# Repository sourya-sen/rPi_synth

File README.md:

**A 32HP EURORACK VIDEO SYNTHESISER**

Update (August 2019): This was the subject of my Master's thesis at Aalto Media Lab and the written thesis can be found and downloaded from [here](https://aaltodoc.aalto.fi/handle/123456789/38068).

The project is currently on hold as I want to upgrade and test with a Raspberry Pi 4 for performance benefits as well as update the hardware with a few fixes and design strategies that were found to be lacking in the current version. However, this version continues to work and if you are looking to build and run one for yourself, I am available to help in any troubleshooting.

[Here is the unit in action as part of my an audiovisual performance at Live Performers Meet 2018.](https://vimeo.com/277031718/060efab75c)

**NOTE: THIS IS STILL WORK IN PROGRESS, PROCEED AT YOUR OWN RISK! TO SUCCESSFULLY RUN, YOU WILL NEED A FABRICATED PCB, A RASPBERRY PI (TESTED WITH RPI 3) AND A EURORACK SETUP.**

## Introduction
This is the central repository for the Hybrid Video Synthesiser project.

The Hybrid Video Synthesiser, as the name suggests, is a video synthesiser that has digital brains by using a Raspberry Pi but can interface with any analog signal for sequencing, manipulating and/or modulating. This version is compatible with Eurorack standards.

It is made up of the following ingredients.
1. A custom PCB to interface between the Eurorack signals and the Raspberry Pi, both EAGLE files and gerbers are made available in the `Hardware` folder.

2. The `rPi_Framework` openFrameworks application that communicates between the hardware and the Raspberry Pi and sends the current state over OSC to the system.

3. The `rPi_videoSynth` openFrameworks application that listens to the OSC communication and runs the visuals. The visuals themselves are fragment shaders that reside in the `/rPi_videoSynth/bin/data/shaders` folder.

4. A illustrator file for the front panel, in the `Hardware` folder.

And the following extras,
* Scripts to auto run on boot on a Raspberry Pi.

* A desktop GUI simulating the hardware OSC communication for testing without the hardware. The `synth_CVTester` openFrameworks application handles that. **IMPORTANT: If using the videoSynth application on the desktop, use the relevant shader headers. See the install notes below - the only difference is using the desktop shader headers instead of the pi headers in step 4.**

The hardware has 4 CV inputs and 8 Gate inputs.

Design wise, the synthesiser is designed to run 8 visual 'systems', as selected by the system toggles in binary fashion. (Refer to conversion chart on front panel).

Each system has 4 sub systems, set by the 2 sub system toggles, again in binary fashion.

The last three toggles/gates switch on/off an effects patch (not implemented yet), a white strobe and enable/disable the final image (useful for black strobes!).

Each can be selected by the toggle switches, but plugging in a gate signal overrides the toggle switch.

Each visual system (and it's subsequent sub system) have 4 parameters that can be controlled by the potentiometers. They also allow CV input and when CV input is present, the potentiometers become attenuators for the CV input. The range and response of the CV inputs (unipolar, bipolar, exponential) can be changed, they're currently hardcoded in the software but will be replaced by an user editable XML file in a later revision.

## About the Hardware
The schematics are available in the `Documentation` folder.

The functionality of the PCB is described below.

The MCP3008 A-to-D chip is used to handle analog inputs coming into the Pi. The CV inputs are taken through an op-amp differential circuit to scale -5V to +5V signals to 0-3.3V Raspberry Pi friendly levels before going into the chip. Any signals below or above the mentioned range is discarded.

The final CV parameter in the software is the value of `potentiometer * CV input` for each channel. When an input CV is missing, the jacks are normalised to +5V to get a constant value of 1.

**Note: Known issue here. As the reference 5V is taken from the Pi's 5V, when plugging in a CV signal, the switching jack doesn't switch cleanly and a different voltage touching the 5V rail of the Pi makes the Pi restart. This will be fixed in the following revision - currently it requires cutting a trace and attaching a 5V regulator from the 12V power rail instead of using the 5V rPi rail.**

The 0-3.3V incoming value is translated to a value of 0-1023 on the software side, which is further mapped to 0.0-1.0 if using the bipolar mode. It is possible to change how the CV is handled, ie, setting it to unipolar by changing a few lines of code, as below:

```
CVin[4].setExponential();
CVin[6].setUnipolar();
CVin[7].setUnipolar();
```

where CVin[0] - CVin[3] are the potentiometer values and CVin[4] - CVin[7] are the CV inputs. The default setting is bipolar. This is currently set in `ofApp::setup()` of `rPi_videoSynth` but will be available to be setup from an XML file in a later revision.

There are two comparators checking the current toggle states of the gates/switches. These go through a multiplexer into the rPi. The comparators are checking for any values above 2.5V but this can be changed by changing R11 and R12.

**Note: Know limitation, the toggles don't activate with very short triggers from the Eurorack, even if the LEDs light up. This _may_ or _may not_ be fixable. To be investigated further. But this arises from the timing differences of the frames per second refresh cycle of the visuals v/s the asynchronous hardware communication.**

## Installing
**Note: I will make a disk image available eventually that can be burned directly to a microSD card, but currently the only way to run this is to install from github.**

This guide assumes you are running the latest version of Raspbian Stretch and have openFrameworks 0.10.0 installed and compiled. This guide also assumes that openFrameworks is installed at `/home/pi/openFrameworks` and the boot options are set to `Console Autologin`.

1. Get the [ofxGPIO](https://github.com/kashimAstro/ofxGPIO) addon.
  * Navigate to `openFrameworks/addons`
  * Clone the ofxGPIO library by typing `git clone https://github.com/kashimAstro/ofxGPIO` and press Enter.

2. Clone this repository.
  * Navigate to `openFrameworks/apps` (Note: Just apps, not myApps).
  * Type `git clone https://github.com/sourya-sen/rPi_synth` and press Enter.

3. Compile **both** the apps separately.
  * Navigate to `openFrameworks/apps/rPi_synth/rPi_Framework`
  * Type `sudo make`, wait for it to finish compiling.
  * Navigate to `openFrameworks/apps/rPi_synth/rPi_videoSynth`
  * Type `sudo make`, wait for it to finish compiling.

4. Copy the header files required to run the shaders.
  * type `cp /home/pi/openFrameworks/apps/rPi_synth/Resources/shaderHeaders/pi/* /home/pi/openFrameworks/apps/rPi_synth/rPi_videoSynth/bin/data/shaders` and hit Enter.

If everything went well, at this point you should be ready to run the video synth!

## Running
The easiest way to run the two softwares that run the video synth is to use the `runSynth` script.

  * Type `cp /home/pi/openFrameworks/apps/rPi_synth/Resources/runSynth.sh /home/pi` and hit Enter.
  * Make sure you're on the bottom level of the pi user account by typing `cd` and hitting Enter.
  * Make the script executable by typing `chmod +x runSynth.sh`
  * Run the synth by typing `./runSynth` and hitting Enter!

To avoid having to run the video synth by running the command with a keyboard every time, you can make the Pi run the `runSynth` script on startup by adding it to the `rc.local` file.

  * Type `sudo nano /etc/rc.local` and hit Enter.
  * Add `sh /home/pi/runSynth.sh &` at the end of the file.
  * Save the file and exit.

Now, every time the Raspberry Pi is switched on, it will boot directly into the synth!

## Writing Own Visuals
If you know how to write fragment shaders, you already know how to write your own visuals! It is also easy to port shaders from [glslsandbox](http://glslsandbox.com/) or [shadertoy](https://www.shadertoy.com/) with some minor changes. The only difference is using the cross platform shader syntax, which you can refer to [here](https://github.com/sourya-sen/oF_crossPlatformShaderExample) for an example. As long as the shaders are named correctly (refer to the existing shader files), they will be available as 'systems' corresponding to the file number. The `.vert` file is common to each fragment shader.

The shaders have multiple uniforms available to them for use. Refer to any preexisting shaders for reference. The shaders are loaded at run time when the application is run and switch accordingly depending on the selected 'system' either through the panel controls or through gate inputs. It is also possible to reload the shaders in the application by pressing `R` on the keyboard. This is handy if you are testing the shaders in the Desktop environment.

In case you need a tutorial on how to write fragment shaders, I'd recommend going through [The Book of Shaders](https://thebookofshaders.com/).

**NOTE: Due to the limited graphics performance capabilities of the Raspberry Pi, it is recommended to thoroughly test each new shader. If a keyboard is attached to the Pi in the testing process, pressing `spacebar` would draw debug strings which will show you the current fps and other relevant data.**

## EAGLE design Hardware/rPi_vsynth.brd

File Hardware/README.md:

The .sch and .brd files here are designs for the PCB, last updated with Eagle 8.5.0.

Please check the main README for known issues with the current hardware revision version.

Library parts used here are from the [Music Thing Modular parts library by Tom Whitwell](https://github.com/TomWhitwell/MTM-Parts-Library) and the [Sparkfun Library](https://github.com/sparkfun/SparkFun-Eagle-Libraries).

The gerber (currently v0.2) files in the zipped folder have been used to fabricate PCBs from [Seeed Fusion PCB Services](https://www.seeedstudio.com/fusion.html) and generated with the Seeed Gerber Generator and the board adheres to the Seeed Design Rules, both found [here](http://support.seeedstudio.com/knowledgebase/articles/422482-fusion-pcb-pcba-order-submission-guidelines).

**[TODO: Add image of the PCB?]**

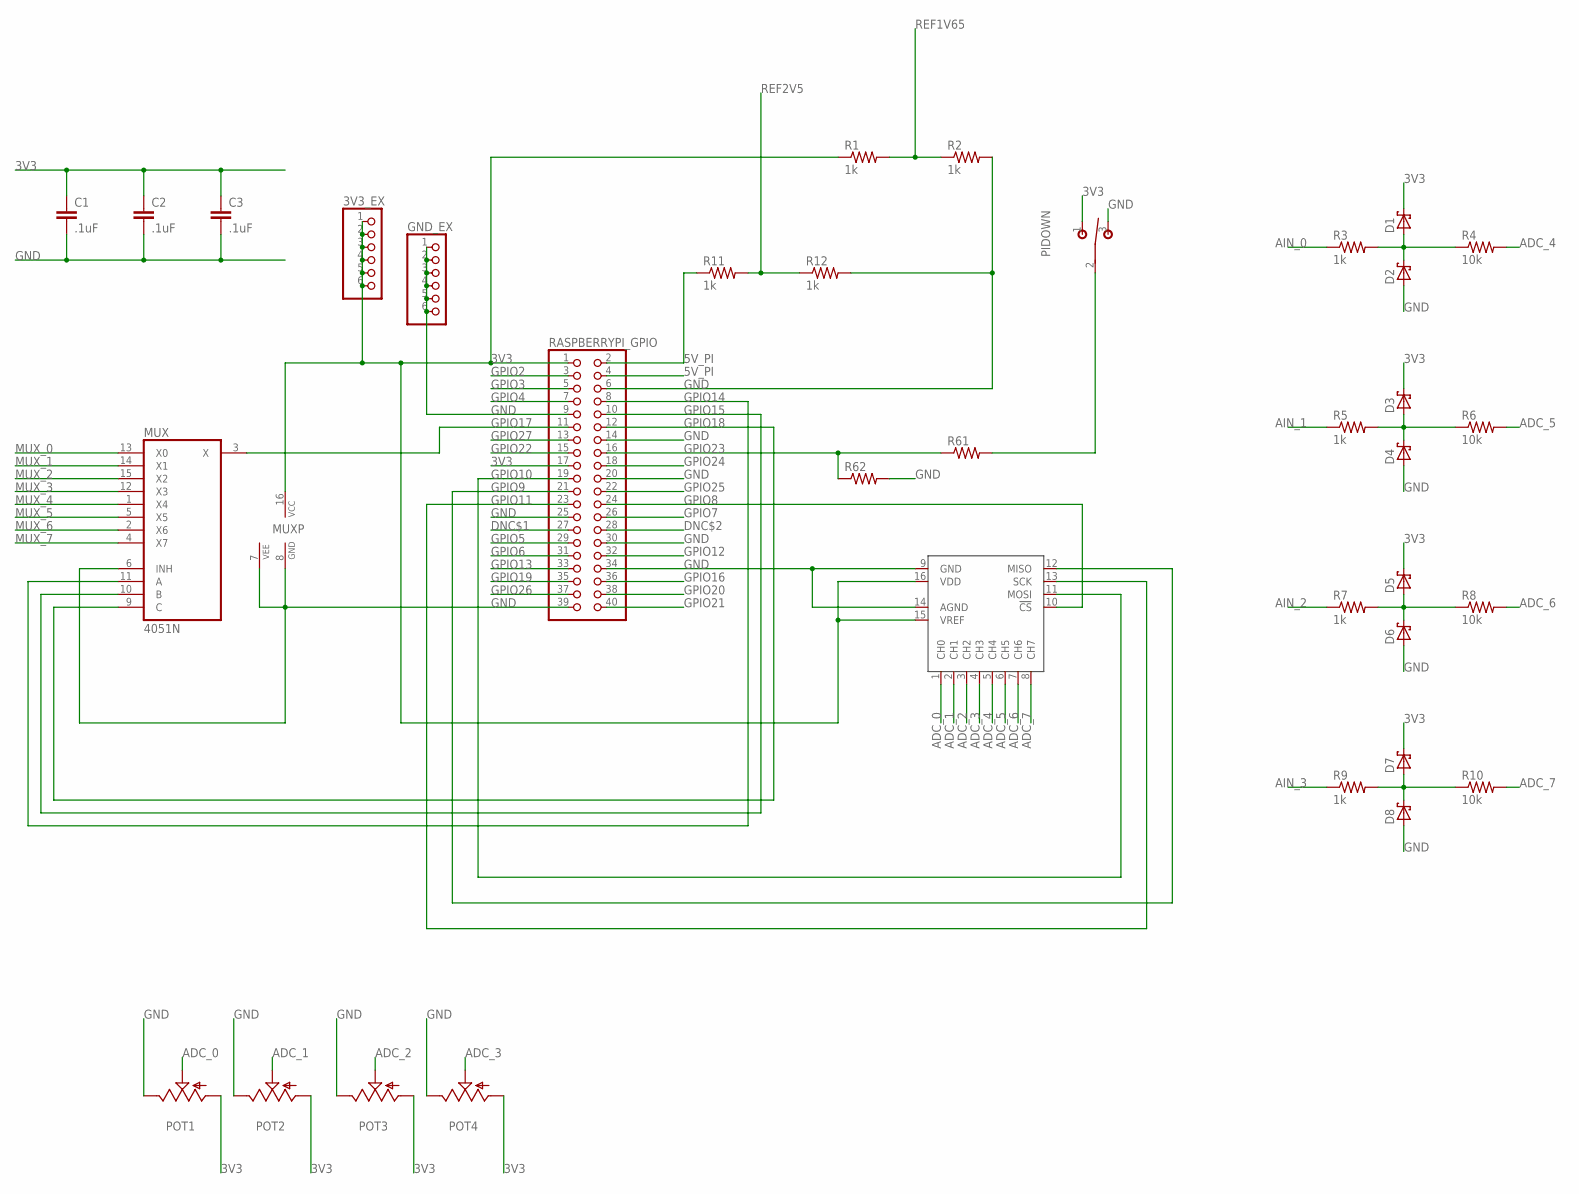
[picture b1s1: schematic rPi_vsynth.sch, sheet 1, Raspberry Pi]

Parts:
3V3_EX: PINHD-1X6B; 1X06-BIG
C1, C2, C3: .1uF; CAP-PTH-SMALL2
D1, D2, D3, D4, D5, D6, D7, D8: SCHOTTKY-DIODEDO35-7; DO35-7
GND_EX: PINHD-1X6B; 1X06-BIG
MCP3008: MCP3008P; DIL16
MUX: 4051N; DIL16
PIDOWN: T-80-T-SPDT-ON-OFF-ON; M9040P
POT1, POT2, POT3, POT4: 9MM_SNAP-IN_POT_; 9MM_SNAP-IN_POT
R1, R2, R3, R5, R7, R9, R11, R12: 1k; AXIAL-0.4
R4, R6, R8, R10: 10k; AXIAL-0.4
R61, R62: RESISTORPTH-1/4W; AXIAL-0.4
RASPBERRYPI_GPIO: PINHD-2X20; 2X20

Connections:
3V3: 3V3_EX.1, 3V3_EX.2, 3V3_EX.3, 3V3_EX.4, 3V3_EX.5, 3V3_EX.6, C1.1, C2.1, C3.1, D1.C, D3.C, D5.C, D7.C, MCP3008.15 (VREF), MCP3008.16 (VDD), MUX.16 (VCC), PIDOWN.1 (O), POT1.1 (A), POT2.1 (A), POT3.1 (A), POT4.1 (A), R1.P$1 (1), RASPBERRYPI_GPIO.1, RASPBERRYPI_GPIO.17; also elsewhere on the board
5V_PI: R11.P$1 (1), RASPBERRYPI_GPIO.2, RASPBERRYPI_GPIO.4; also elsewhere on the board
ADC_0: MCP3008.1 (CH0), POT1.2 (S)
ADC_1: MCP3008.2 (CH1), POT2.2 (S)
ADC_2: MCP3008.3 (CH2), POT3.2 (S)
ADC_3: MCP3008.4 (CH3), POT4.2 (S)
ADC_4: MCP3008.5 (CH4), R4.P$2 (2)
ADC_5: MCP3008.6 (CH5), R6.P$2 (2)
ADC_6: MCP3008.7 (CH6), R8.P$2 (2)
ADC_7: MCP3008.8 (CH7), R10.P$2 (2)
AIN_0: R3.P$1 (1); also elsewhere on the board
AIN_1: R5.P$1 (1); also elsewhere on the board
AIN_2: R7.P$1 (1); also elsewhere on the board
AIN_3: R9.P$1 (1); also elsewhere on the board
DNC$1: RASPBERRYPI_GPIO.27
DNC$2: RASPBERRYPI_GPIO.28
GND: C1.2, C2.2, C3.2, D2.A, D4.A, D6.A, D8.A, GND_EX.1, GND_EX.2, GND_EX.3, GND_EX.4, GND_EX.5, GND_EX.6, MCP3008.9 (GND), MCP3008.14 (AGND), MUX.6 (INH), MUX.7 (VEE), MUX.8 (GND), PIDOWN.3 (S), POT1.3 (E), POT2.3 (E), POT3.3 (E), POT4.3 (E), R2.P$2 (2), R12.P$2 (2), R62.P$2 (2), RASPBERRYPI_GPIO.6, RASPBERRYPI_GPIO.9, RASPBERRYPI_GPIO.14, RASPBERRYPI_GPIO.20, RASPBERRYPI_GPIO.25, RASPBERRYPI_GPIO.30, RASPBERRYPI_GPIO.34, RASPBERRYPI_GPIO.39; also elsewhere on the board
GPIO2: RASPBERRYPI_GPIO.3
GPIO3: RASPBERRYPI_GPIO.5
GPIO4: RASPBERRYPI_GPIO.7
GPIO5: RASPBERRYPI_GPIO.29
GPIO6: RASPBERRYPI_GPIO.31
GPIO7: RASPBERRYPI_GPIO.26
GPIO8: MCP3008.10 (!CS), RASPBERRYPI_GPIO.24
GPIO9: MCP3008.12 (MISO), RASPBERRYPI_GPIO.21
GPIO10: MCP3008.11 (MOSI), RASPBERRYPI_GPIO.19
GPIO11: MCP3008.13 (SCK), RASPBERRYPI_GPIO.23
GPIO12: RASPBERRYPI_GPIO.32
GPIO13: RASPBERRYPI_GPIO.33
GPIO14: MUX.11 (A), RASPBERRYPI_GPIO.8
GPIO15: MUX.10 (B), RASPBERRYPI_GPIO.10
GPIO16: RASPBERRYPI_GPIO.36
GPIO17: MUX.3 (X), RASPBERRYPI_GPIO.11
GPIO18: MUX.9 (C), RASPBERRYPI_GPIO.12
GPIO19: RASPBERRYPI_GPIO.35
GPIO20: RASPBERRYPI_GPIO.38
GPIO21: RASPBERRYPI_GPIO.40
GPIO22: RASPBERRYPI_GPIO.15
GPIO23: R61.P$1 (1), R62.P$1 (1), RASPBERRYPI_GPIO.16
GPIO24: RASPBERRYPI_GPIO.18
GPIO25: RASPBERRYPI_GPIO.22
GPIO26: RASPBERRYPI_GPIO.37
GPIO27: RASPBERRYPI_GPIO.13
MUX_0: MUX.13 (X0); also elsewhere on the board
MUX_1: MUX.14 (X1); also elsewhere on the board
MUX_2: MUX.15 (X2); also elsewhere on the board
MUX_3: MUX.12 (X3); also elsewhere on the board
MUX_4: MUX.1 (X4); also elsewhere on the board
MUX_5: MUX.5 (X5); also elsewhere on the board
MUX_6: MUX.2 (X6); also elsewhere on the board
MUX_7: MUX.4 (X7); also elsewhere on the board
unnamed: D1.A, D2.C, R3.P$2 (2), R4.P$1 (1)
unnamed: D3.A, D4.C, R5.P$2 (2), R6.P$1 (1)
unnamed: D5.A, D6.C, R7.P$2 (2), R8.P$1 (1)
unnamed: D7.A, D8.C, R9.P$2 (2), R10.P$1 (1)
unnamed: PIDOWN.2, R61.P$2 (2)
REF1V65: R1.P$2 (2), R2.P$1 (1); also elsewhere on the board
REF2V5: R11.P$2 (2), R12.P$1 (1); also elsewhere on the board

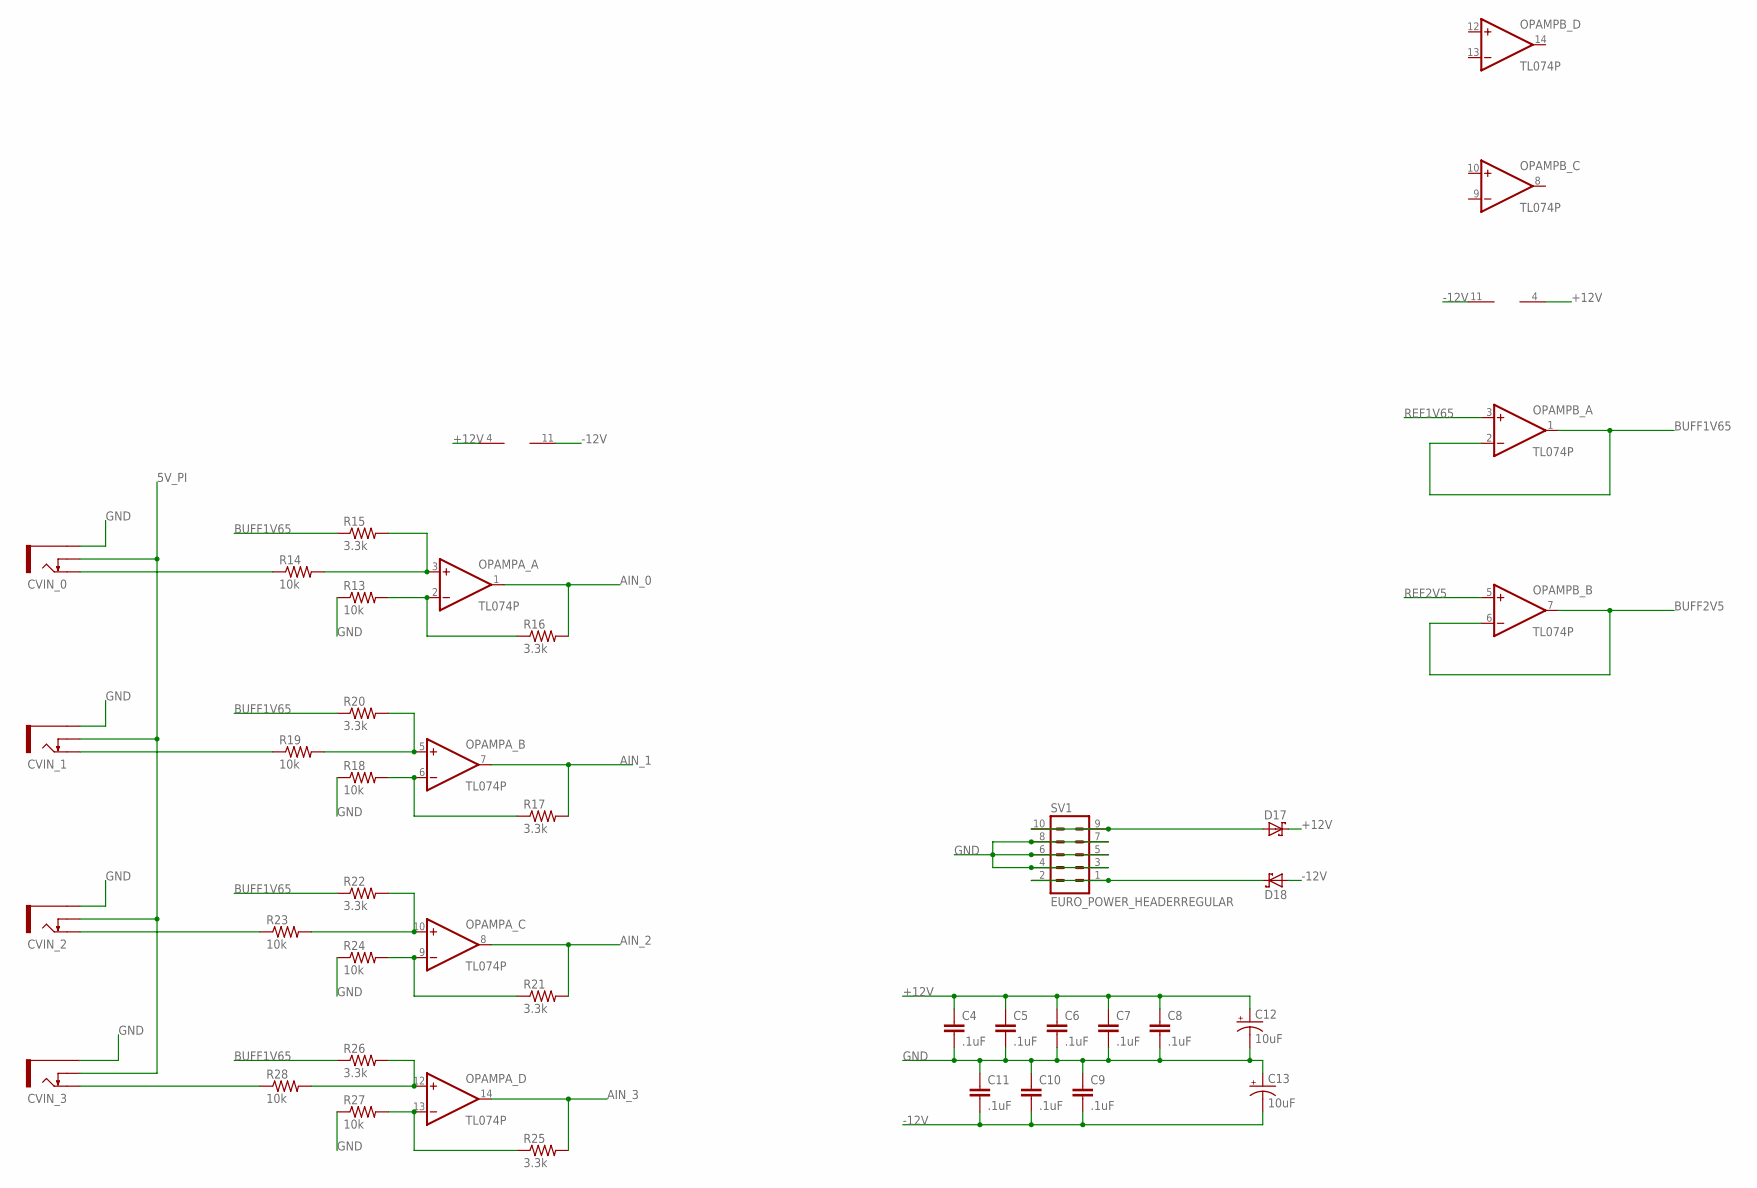
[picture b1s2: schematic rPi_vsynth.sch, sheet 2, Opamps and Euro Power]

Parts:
C4, C5, C6, C7, C8, C9, C10, C11: .1uF; CAP-PTH-SMALL2
C12, C13: 10uF; CPOL-RADIAL-10UF-25V
CVIN_0, CVIN_1, CVIN_2, CVIN_3: THONKICONNOLD; THONKICONN
D17, D18: SCHOTTKY-DIODEDO35-7; DO35-7
OPAMPA_: TL074P; DIL14
OPAMPB_: TL074P; DIL14
R13, R14, R18, R19, R23, R24, R27, R28: 10k; AXIAL-0.4
R15, R16, R17, R20, R21, R22, R25, R26: 3.3k; AXIAL-0.4
SV1: EURO_POWER_HEADERREGULAR; EURO_POWER_HEADER

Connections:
5V_PI: CVIN_0.P$2_SWITCH (SWITCH), CVIN_1.P$2_SWITCH (SWITCH), CVIN_2.P$2_SWITCH (SWITCH), CVIN_3.P$2_SWITCH (SWITCH); also elsewhere on the board
+12V: C4.1, C5.1, C6.1, C7.1, C8.1, C12.1 (+), D17.C, OPAMPA_.4 (V+), OPAMPB_.4 (V+); also elsewhere on the board
-12V: C9.2, C10.2, C11.2, C13.2 (-), D18.A, OPAMPA_.11 (V-), OPAMPB_.11 (V-)
AIN_0: OPAMPA_.1 (OUT), R16.P$2 (2); also elsewhere on the board
AIN_1: OPAMPA_.7 (OUT), R17.P$2 (2); also elsewhere on the board
AIN_2: OPAMPA_.8 (OUT), R21.P$2 (2); also elsewhere on the board
AIN_3: OPAMPA_.14 (OUT), R25.P$2 (2); also elsewhere on the board
BUFF1V65: OPAMPB_.1 (OUT), OPAMPB_.2 (-IN), R15.P$1 (1), R20.P$1 (1), R22.P$1 (1), R26.P$1 (1)
BUFF2V5: OPAMPB_.6 (-IN), OPAMPB_.7 (OUT); also elsewhere on the board
GND: C4.2, C5.2, C6.2, C7.2, C8.2, C9.1, C10.1, C11.1, C12.2 (-), C13.1 (+), CVIN_0.P$1_SLEEVE (SLEEVE), CVIN_1.P$1_SLEEVE (SLEEVE), CVIN_2.P$1_SLEEVE (SLEEVE), CVIN_3.P$1_SLEEVE (SLEEVE), R13.P$1 (1), R18.P$1 (1), R24.P$1 (1), R27.P$1 (1), SV1.3, SV1.4, SV1.5, SV1.6, SV1.7, SV1.8; also elsewhere on the board
unnamed: OPAMPA_.2 (-IN), R13.P$2 (2), R16.P$1 (1)
unnamed: CVIN_0.P$3_TIP (TIP), R14.P$1 (1)
unnamed: OPAMPA_.6 (-IN), R17.P$1 (1), R18.P$2 (2)
unnamed: OPAMPA_.3 (+IN), R14.P$2 (2), R15.P$2 (2)
unnamed: OPAMPA_.9 (-IN), R21.P$1 (1), R24.P$2 (2)
unnamed: OPAMPA_.5 (+IN), R19.P$2 (2), R20.P$2 (2)
unnamed: OPAMPA_.10 (+IN), R22.P$2 (2), R23.P$2 (2)
unnamed: CVIN_1.P$3_TIP (TIP), R19.P$1 (1)
unnamed: OPAMPA_.13 (-IN), R25.P$1 (1), R27.P$2 (2)
unnamed: CVIN_2.P$3_TIP (TIP), R23.P$1 (1)
unnamed: CVIN_3.P$3_TIP (TIP), R28.P$1 (1)
unnamed: OPAMPA_.12 (+IN), R26.P$2 (2), R28.P$2 (2)
unnamed: D17.A, SV1.9, SV1.10
unnamed: D18.C, SV1.1, SV1.2
REF1V65: OPAMPB_.3 (+IN); also elsewhere on the board
REF2V5: OPAMPB_.5 (+IN); also elsewhere on the board

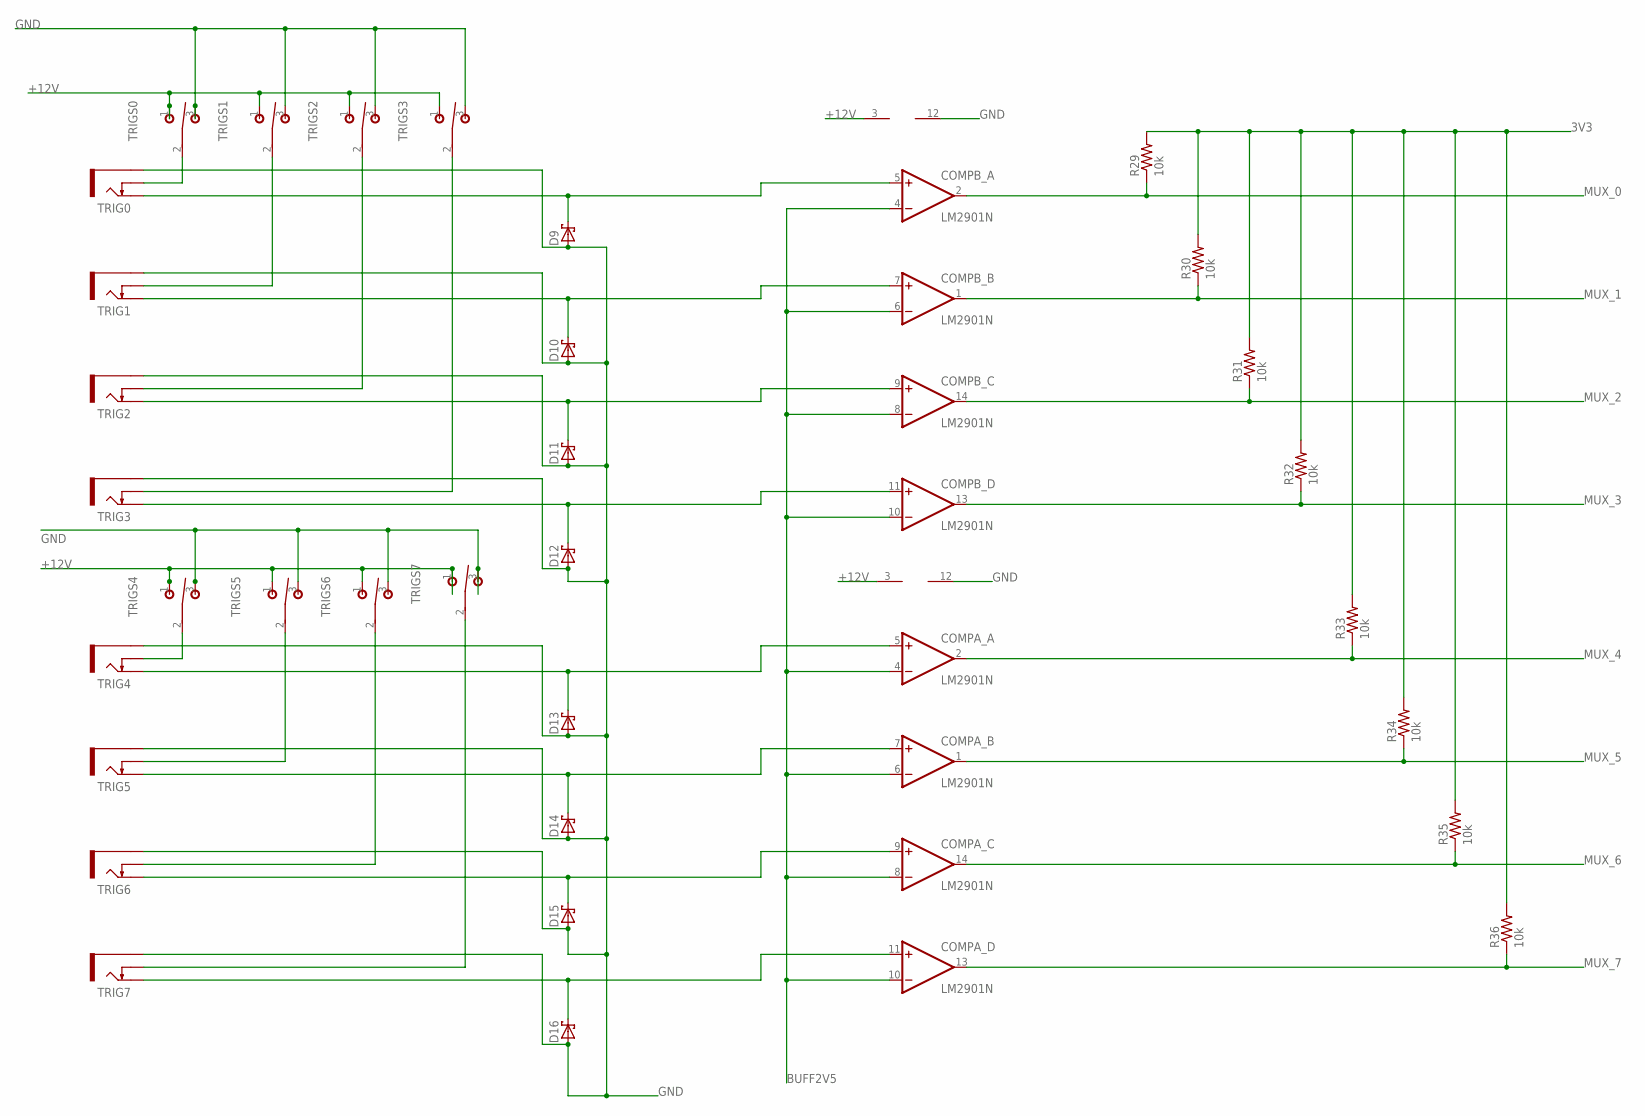
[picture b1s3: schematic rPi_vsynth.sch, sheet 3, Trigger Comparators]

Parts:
COMPA_: LM2901N; DIL14
COMPB_: LM2901N; DIL14
D9, D10, D11, D12, D13, D14, D15, D16: SCHOTTKY-DIODEDO35-7; DO35-7
R29, R30, R31, R32, R33, R34, R35, R36: 10k; AXIAL-0.4
TRIG0, TRIG1, TRIG2, TRIG3, TRIG4, TRIG5, TRIG6, TRIG7: THONKICONNOLD; THONKICONN
TRIGS0, TRIGS1, TRIGS2, TRIGS3, TRIGS4, TRIGS5, TRIGS6, TRIGS7: T-80-T-SPDT-ON-OFF-ON; M9040P

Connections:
3V3: R29.P$2 (2), R30.P$2 (2), R31.P$2 (2), R32.P$2 (2), R33.P$2 (2), R34.P$2 (2), R35.P$2 (2), R36.P$2 (2); also elsewhere on the board
+12V: COMPA_.3 (V+), COMPB_.3 (V+), TRIGS0.1 (O), TRIGS1.1 (O), TRIGS2.1 (O), TRIGS3.1 (O), TRIGS4.1 (O), TRIGS5.1 (O), TRIGS6.1 (O), TRIGS7.1 (O); also elsewhere on the board
BUFF2V5: COMPA_.4 (-IN), COMPA_.6 (-IN), COMPA_.8 (-IN), COMPA_.10 (-IN), COMPB_.4 (-IN), COMPB_.6 (-IN), COMPB_.8 (-IN), COMPB_.10 (-IN); also elsewhere on the board
GND: COMPA_.12 (V-), COMPB_.12 (V-), D9.A, D10.A, D11.A, D12.A, D13.A, D14.A, D15.A, D16.A, TRIG0.P$1_SLEEVE (SLEEVE), TRIG1.P$1_SLEEVE (SLEEVE), TRIG2.P$1_SLEEVE (SLEEVE), TRIG3.P$1_SLEEVE (SLEEVE), TRIG4.P$1_SLEEVE (SLEEVE), TRIG5.P$1_SLEEVE (SLEEVE), TRIG6.P$1_SLEEVE (SLEEVE), TRIG7.P$1_SLEEVE (SLEEVE), TRIGS0.3 (S), TRIGS1.3 (S), TRIGS2.3 (S), TRIGS3.3 (S), TRIGS4.3 (S), TRIGS5.3 (S), TRIGS6.3 (S), TRIGS7.3 (S); also elsewhere on the board
MUX_0: COMPB_.2 (OUT), R29.P$1 (1); also elsewhere on the board
MUX_1: COMPB_.1 (OUT), R30.P$1 (1); also elsewhere on the board
MUX_2: COMPB_.14 (OUT), R31.P$1 (1); also elsewhere on the board
MUX_3: COMPB_.13 (OUT), R32.P$1 (1); also elsewhere on the board
MUX_4: COMPA_.2 (OUT), R33.P$1 (1); also elsewhere on the board
MUX_5: COMPA_.1 (OUT), R34.P$1 (1); also elsewhere on the board
MUX_6: COMPA_.14 (OUT), R35.P$1 (1); also elsewhere on the board
MUX_7: COMPA_.13 (OUT), R36.P$1 (1); also elsewhere on the board
unnamed: TRIG0.P$2_SWITCH (SWITCH), TRIGS0.2
unnamed: TRIG1.P$2_SWITCH (SWITCH), TRIGS1.2
unnamed: TRIG2.P$2_SWITCH (SWITCH), TRIGS2.2
unnamed: TRIG3.P$2_SWITCH (SWITCH), TRIGS3.2
unnamed: TRIG4.P$2_SWITCH (SWITCH), TRIGS4.2
unnamed: TRIG5.P$2_SWITCH (SWITCH), TRIGS5.2
unnamed: TRIG6.P$2_SWITCH (SWITCH), TRIGS6.2
unnamed: TRIG7.P$2_SWITCH (SWITCH), TRIGS7.2
unnamed: COMPB_.5 (+IN), D9.C, TRIG0.P$3_TIP (TIP)
unnamed: COMPB_.7 (+IN), D10.C, TRIG1.P$3_TIP (TIP)
unnamed: COMPB_.9 (+IN), D11.C, TRIG2.P$3_TIP (TIP)
unnamed: COMPB_.11 (+IN), D12.C, TRIG3.P$3_TIP (TIP)
unnamed: COMPA_.5 (+IN), D13.C, TRIG4.P$3_TIP (TIP)
unnamed: COMPA_.7 (+IN), D14.C, TRIG5.P$3_TIP (TIP)
unnamed: COMPA_.9 (+IN), D15.C, TRIG6.P$3_TIP (TIP)
unnamed: COMPA_.11 (+IN), D16.C, TRIG7.P$3_TIP (TIP)

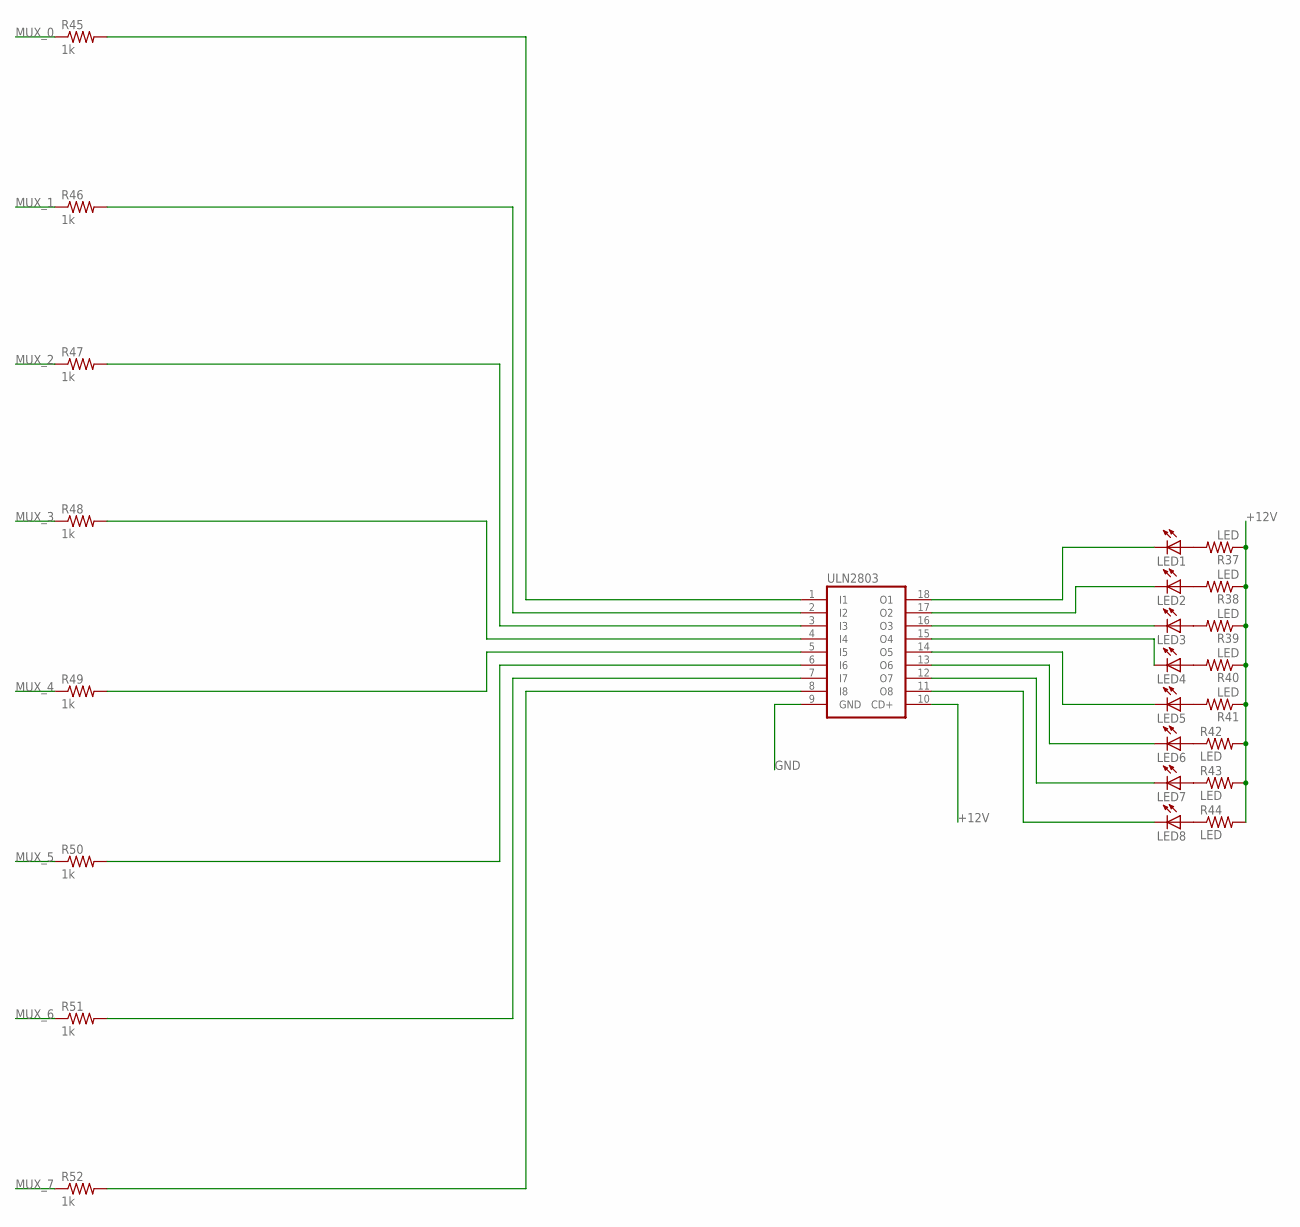
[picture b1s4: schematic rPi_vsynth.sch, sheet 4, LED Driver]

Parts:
LED1, LED2, LED3, LED4, LED5, LED6, LED7, LED8: LED3MM
R37, R38, R39, R40, R41, R42, R43, R44: LED; AXIAL-0.4
R45, R46, R47, R48, R49, R50, R51, R52: 1k; AXIAL-0.4
ULN2803: ULN2803A; DIL18

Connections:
+12V: R37.P$1 (1), R38.P$1 (1), R39.P$1 (1), R40.P$1 (1), R41.P$1 (1), R42.P$2 (2), R43.P$2 (2), R44.P$2 (2), ULN2803.10 (CD+); also elsewhere on the board
GND: ULN2803.9 (GND); also elsewhere on the board
MUX_0: R45.P$1 (1); also elsewhere on the board
MUX_1: R46.P$1 (1); also elsewhere on the board
MUX_2: R47.P$1 (1); also elsewhere on the board
MUX_3: R48.P$1 (1); also elsewhere on the board
MUX_4: R49.P$1 (1); also elsewhere on the board
MUX_5: R50.P$1 (1); also elsewhere on the board
MUX_6: R51.P$1 (1); also elsewhere on the board
MUX_7: R52.P$1 (1); also elsewhere on the board
unnamed: LED1.A, R37.P$2 (2)
unnamed: LED2.A, R38.P$2 (2)
unnamed: LED3.A, R39.P$2 (2)
unnamed: LED4.A, R40.P$2 (2)
unnamed: LED5.A, R41.P$2 (2)
unnamed: LED6.A, R42.P$1 (1)
unnamed: LED7.A, R43.P$1 (1)
unnamed: LED8.A, R44.P$1 (1)
unnamed: LED3.K (C), ULN2803.16 (O3)
unnamed: R45.P$2 (2), ULN2803.1 (I1)
unnamed: LED1.K (C), ULN2803.18 (O1)
unnamed: LED2.K (C), ULN2803.17 (O2)
unnamed: LED4.K (C), ULN2803.15 (O4)
unnamed: LED5.K (C), ULN2803.14 (O5)
unnamed: LED6.K (C), ULN2803.13 (O6)
unnamed: LED7.K (C), ULN2803.12 (O7)
unnamed: LED8.K (C), ULN2803.11 (O8)
unnamed: R52.P$2 (2), ULN2803.8 (I8)
unnamed: R46.P$2 (2), ULN2803.2 (I2)
unnamed: R47.P$2 (2), ULN2803.3 (I3)
unnamed: R48.P$2 (2), ULN2803.4 (I4)
unnamed: R49.P$2 (2), ULN2803.5 (I5)
unnamed: R50.P$2 (2), ULN2803.6 (I6)
unnamed: R51.P$2 (2), ULN2803.7 (I7)

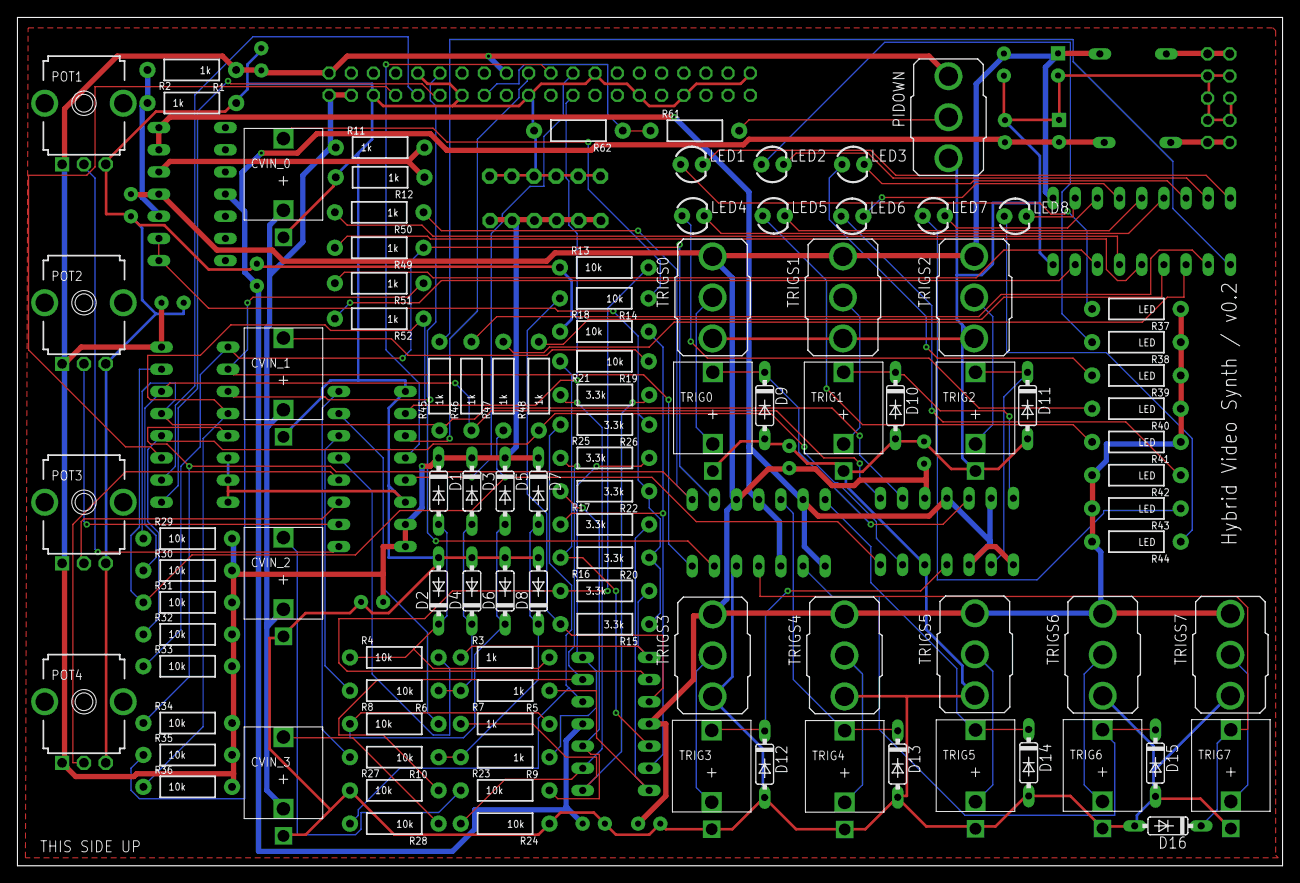
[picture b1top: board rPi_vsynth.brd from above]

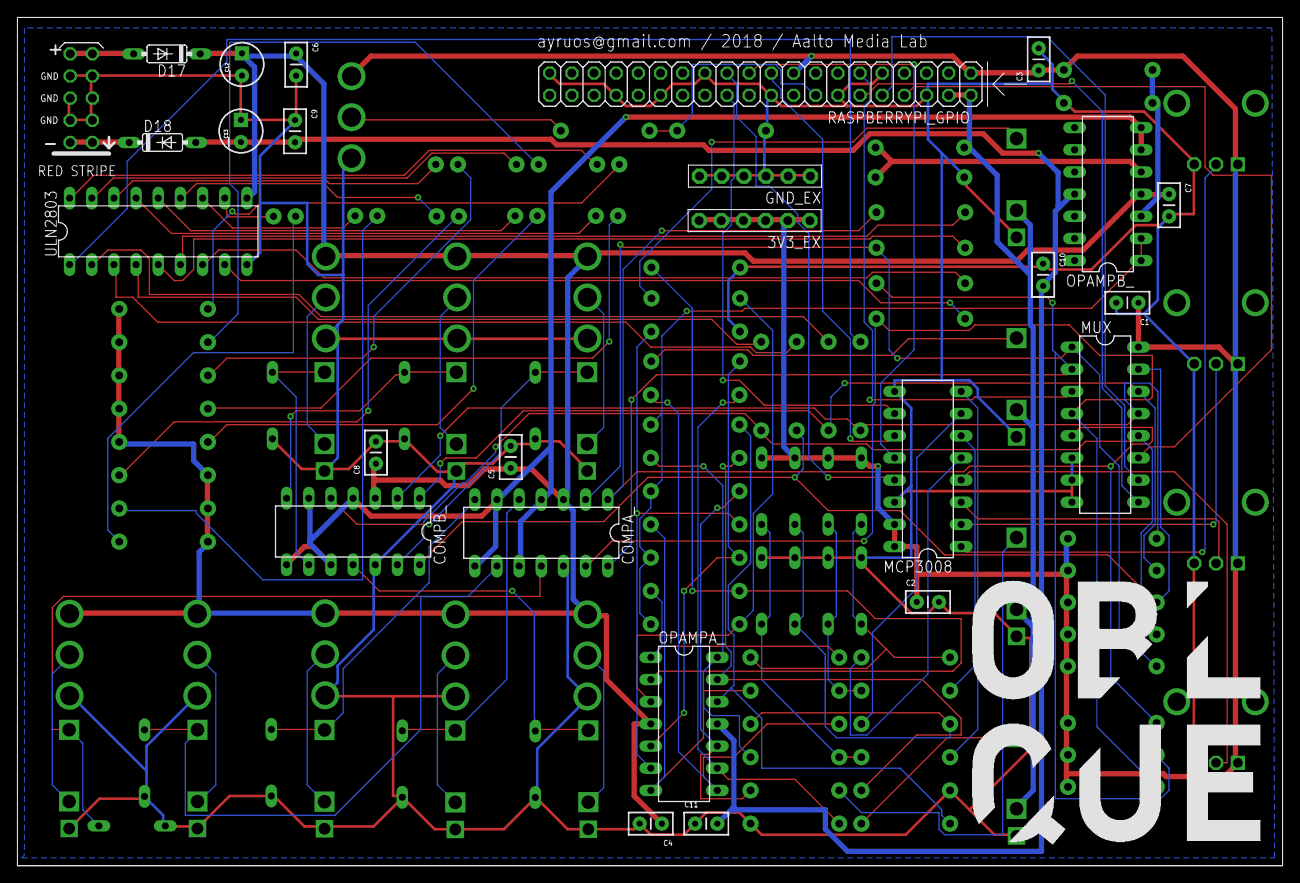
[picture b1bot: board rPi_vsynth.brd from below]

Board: 2 copper layers, 145.0 x 97.2 mm, 129 parts (26 on the bottom side), 97 nets.

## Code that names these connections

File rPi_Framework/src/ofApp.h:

#pragma once

#include "ofMain.h"
#include "ofxGPIO.h"
#include "ofxOsc.h"

#define HOST "localhost"
#define PORT 12345

class ofApp : public ofBaseApp{

	public:
		void setup();
		void update();
		void draw();
		void exit();

		void keyPressed(int key);
		void keyReleased(int key);
		void mouseMoved(int x, int y );
		void mouseDragged(int x, int y, int button);
		void mousePressed(int x, int y, int button);
		void mouseReleased(int x, int y, int button);
		void mouseEntered(int x, int y);
		void mouseExited(int x, int y);
		void windowResized(int w, int h);
		void dragEvent(ofDragInfo dragInfo);
		void gotMessage(ofMessage msg);

		MCP a2d;
		MCP_DESC chip = MCP3008;
		vector<int> analogIn;

		GPIO gpio14, gpio15, gpio17, gpio18;
		vector<string> mux;

		//these will be sent over OSC
		int o_system, lastSystem;
		int o_subSystem;
		bool o_fx0, o_fx1, o_fx2;
		vector<float> o_cv;

	
		ofxOscSender sender;

};

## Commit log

2017-12-30 makefiles
2017-12-30 ofxGPIO
2017-12-30 test and troubleshoot
2017-12-30 add variables to send via osc
2017-12-30 fix type conversions
2017-12-30 add OSC
2017-12-30 update addons
2017-12-30 fix header file
2017-12-30 minor fix
2017-12-30 ofAppNoWindow
2017-12-30 test succesful!
2017-12-30 add all OSC
2017-12-30 fix comment typo
2018-01-25 add couts for debugging
2018-01-25 troubleshooting w pcb code changes
2018-01-31 change osc outputs
2018-01-31 make OSC more generic
2018-01-31 init main app
2018-01-31 init OSC receiver
2018-01-31 make no window again
2018-01-31 fix osc bug
2018-01-31 more osc fixes
2018-01-31 add CV prints
2018-01-31 debug draws
2018-01-31 fix scaling of debug
2018-02-19 fix OSC receiver typos
2018-02-19 init shader code, doesn't work yet
2018-02-19 more tests, no display on Mac yet
2018-02-20 try arturo main + shader code
2018-02-20 compile and run on Pi
2018-02-20 change GLES to GL_ES
2018-02-20 rever last commit
2018-02-20 rever
2018-02-20 test with pragma include
2018-02-20 clean ;
2018-02-21 move shader header code unique files
2018-02-21 add readme, not tested on Pi yet
2018-02-21 fix pi shader headers
2018-02-21 fix README
2018-02-21 first CV test frag shader
2018-03-01 move draw to an fbo, add missing shaders
2018-03-01 succesfully test on rPi
2018-03-01 testShaders
2018-03-01 remove duplicate line
2018-03-01 remove heavy shader
2018-03-01 reinit shader
2018-03-01 change shaders to check on rPi
2018-03-01 add framerate and res to debug and update shadertoy shader
2018-03-01 more shader tests
2018-03-01 make floats smaller
2018-03-01 test simplified math
2018-03-01 shaders with more cleanups
2018-03-01 fix float
2018-03-01 make all nos float
2018-03-07 rPi fullscreen + rorsah shader
2018-03-07 fix windowMode typo
2018-03-07 fix resolution scaling
2018-03-07 make shader code lighter
2018-03-07 more res nonsense
2018-03-07 fix typo
2018-03-07 rpi build
2018-03-07 clean stuff to test fps
2018-03-07 new shader
2018-03-07 cleanup runSystem code
2018-03-07 noise Shader
2018-03-07 try nonfullscreen
2018-03-07 set FBO format
2018-03-08 get working on Jessie
2018-03-08 try another shader
2018-03-08 fix floats
2018-03-08 FRAG
2018-03-08 add CV
2018-03-08 another trial
2018-03-08 glslsandbox
2018-03-09 performace test
2018-03-09 add CV to shader4 and keyboard to reload shaders
2018-03-09 check fullscreen performance
2018-03-09 rever to 1024 768
2018-03-09 CV controls to noise shader
2018-03-09 latest build
2018-03-12 add cout for headless testing
2018-03-12 latest build with v2 hw test
2018-03-13 rPi HW Tests
2018-03-13 send system osc only if changed
2018-03-13 add sleep
2018-03-13 check stability with fps
2018-03-13 hacky fix?
2018-03-13 .h wasn't saved
2018-03-13 send once every 40ms
2018-03-13 add more delay
2018-03-13 check w/ couts
2018-03-13 check with draw
2018-03-17 edit framework to send packed OSC messages
2018-03-17 update videoSynth with new OSC implemenetation
2018-03-17 rPi build + run
2018-03-17 fix osc address
2018-03-17 rPi test
2018-03-17 try setting up the osc message in header?
2018-03-17 more osc tests, no success yet
2018-03-17 try bundle == true
2018-03-17 change osc
2018-03-23 cleanup Framework for master commit
2018-03-23 add pointer to shader on the synth
2018-03-23 fix shader readme file
2018-04-25 write logic for drawing Fbos
2018-04-25 enable fbo
2018-04-25 strober and enabler succesfull run
2018-04-25 change shader 1
2018-04-25 fix frag1 to run on Pi
2018-04-25 add subsystem to frag1
2018-04-25 clean switch statements
2018-04-25 test extensions
2018-04-25 check performance without if
2018-04-25 test shader with pp if statements
2018-04-25 try Johns smart method
2018-04-25 sadface
2018-04-26 make subSystems work in sys2
2018-04-26 make class for handling CV
2018-04-26 change CV to the new class
2018-04-26 fix debug of CVs breaking compiling
2018-04-26 run new CV class on rPi
2018-04-26 add methods to enable expo and uni functions
2018-04-26 set CVs to be expo and uni etc
2018-04-26 change OSC handling to fix CV scaling errors with uni CVs
2018-04-26 Framework update
2018-04-26 fix stupid math
2018-04-26 rPi run
2018-04-29 rPi commits
2018-05-03 rPi fullscreen
2018-05-03 change shader 01 for subSytem
2018-05-03 add int
2018-05-03 modulo
2018-05-03 helix2
2018-05-03 change brightness
2018-05-03 subsystem init
2018-05-03 add float
2018-05-03 ss to noise
2018-05-03 3 ++
2018-05-03 3 +++
2018-05-03 3 time mult
2018-05-03 fix ints
2018-05-03 cmaketemp ignoreo of fx
2018-05-21 Write initial documentation
2018-05-21 minor formatting fix
2018-05-22 upgrade to oF_0.10.0
2018-05-23 finish writing README/Installing
2018-05-23 fix gitignore and add platform specific glsl files
2018-05-23 add runSynth script and running info to README
2018-05-23 minor edits
2018-05-23 fix the rc local entry
2018-05-23 fix typos
2018-05-24 add CV tester desktop app
2018-05-24 test desktop version
2018-05-24 change TODO status of desktop version
2018-05-24 Add Eagle stuff to .gitignore
2018-05-24 add hardware board files to repo
2018-05-24 hardware readme
2018-05-24 add zipped gerbers
2018-05-24 minor readme edit
2018-06-03 switch res to 1280x720
2018-06-08 minor README fix
2018-06-20 Create LICENSE
2018-09-10 update scaling behaviour to full screen proportional
2018-09-10 lock FPS back to 25
2018-09-10 add shader five
2018-09-14 add CV functions to shader5
2018-09-14 add shader6
2018-09-14 fix fbo drawing logic
2018-09-14 add invert shader - doesn't work yet
2018-09-30 change shader params
2018-10-01 change alpha in the last CV in
2019-04-15 update documentation and add panel
2019-04-15 add panel file
2019-04-15 edits
2019-09-13 fix vimeo link
2019-11-15 shader formatting cleanup
2019-11-15 shader shuffling and updates
2019-11-15 more edits
2019-11-19 new shaders from tbof
2019-11-23 fixing egl shaders
2019-11-23 rpi shaders upto 4 working
2019-11-23 all systems operational
2019-11-28 swap systems 3 and 4

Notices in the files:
parts and their libraries:
SparkFun: Licensing: CC v3.0 Share-Alike You are welcome to use this library for commercial purposes.
